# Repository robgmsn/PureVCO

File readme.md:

View this project on [CADLAB.io](https://cadlab.io/project/24199). 

DESIGN STATUS: Awaiting testing - Ready for beta testing.

VCO Updated to V3.1 14/04/21.

Mixer section changed from Average to Sum. Mix Out is now inversion of individual outs. Might be useful?
Resistor values around mixer section reduced to 10k, inline with low noise techniques.

To do:
Final test build

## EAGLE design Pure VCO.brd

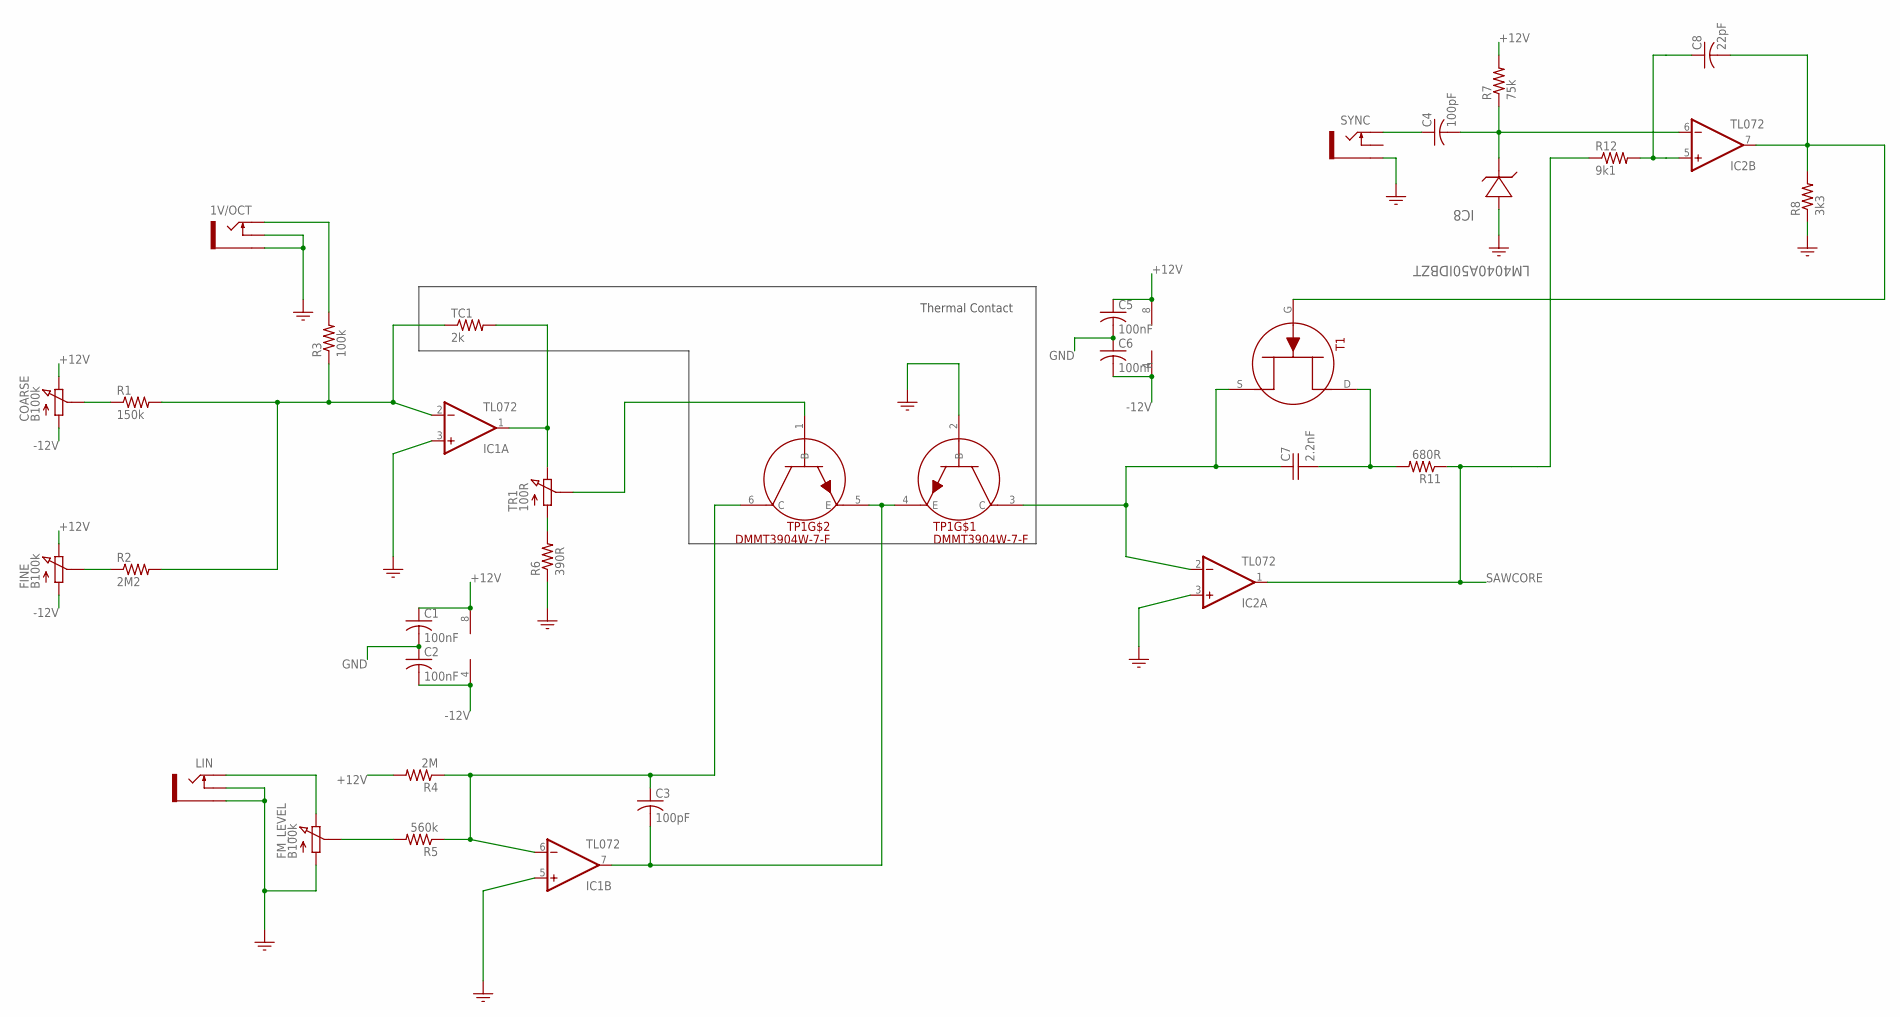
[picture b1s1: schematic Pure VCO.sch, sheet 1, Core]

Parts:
1V/OCT: PJ301M-12
C1, C2, C5, C6: 100nF; C0805
C3, C4: 100pF; C0805
C7: 2.2nF; POLY_CAP
C8: 22pF; C0805
COARSE: B100k; POT_9MM_RED_KNOB
FINE: B100k; POT_9MM_RED_MXR_KNOB
FM_LEVEL: B100k; POT_9MM_GREEN_KNOB
IC1, IC2: TL072; SO08
IC8: LM4040A50IDBZT; SOT95P237X112-3N
LIN: PJ301M-12
R1: 150k; R0805
R2: 2M2; R0805
R3: 100k; R0805
R4: 2M; R0805
R5: 560k; R0805
R6: 390R; R0805
R7: 75k; R0805
R8: 3k3; R0805
R11: 680R; R0805
R12: 9k1; R0805
SYNC: PJ301M-12
T1: MMBFJ309; N_CHN
TC1: 2k; 0207/8.5
TP1: DMMT3904W-7-F; TRANS_PAIR
TR1: 100R; TRIMMER_TH

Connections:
+12V: C1.1, C5.1, COARSE.P$3 (3), FINE.P$3 (3), IC1.8 (V+), IC2.8 (V+), R4.2, R7.2; also elsewhere on the board
-12V: C2.2, C6.2, COARSE.P$1 (1), FINE.P$1 (1), IC1.4 (V-), IC2.4 (V-); also elsewhere on the board
GND: 1V/OCT.GND (SLEEVE), 1V/OCT.NORM (SWITCH), C1.2, C2.1, C5.2, C6.1, FM_LEVEL.P$1 (1), IC1.3 (+IN), IC1.5 (+IN), IC2.3 (+IN), IC8.2 (ANODE), LIN.GND (SLEEVE), LIN.NORM (SWITCH), R6.1, R8.1, SYNC.GND (SLEEVE), TP1.2 (B); also elsewhere on the board
unnamed: COARSE.P$2 (2), R1.1
unnamed: IC1.2 (-IN), R1.2, R2.2, R3.1, TC1.1
unnamed: FINE.P$2 (2), R2.1
unnamed: IC1.1 (OUT), TC1.2, TR1.3
unnamed: R6.2, TR1.1
unnamed: 1V/OCT.TIP, R3.2
unnamed: TP1.1 (B), TR1.2
unnamed: C7.2 (-), R11.2, T1.D
unnamed: C3.1, IC1.6 (-IN), R4.1, R5.1, TP1.6 (C)
unnamed: C7.1 (+), IC2.2 (-IN), T1.S, TP1.3 (C)
unnamed: FM_LEVEL.P$3 (3), LIN.TIP
unnamed: C8.1, IC2.5 (+IN), R12.2
unnamed: FM_LEVEL.P$2 (2), R5.2
unnamed: C3.2, IC1.7 (OUT), TP1.4 (E), TP1.5 (E)
unnamed: C8.2, IC2.7 (OUT), R8.2, T1.G
unnamed: C4.1, SYNC.TIP
unnamed: C4.2, IC2.6 (-IN), IC8.1 (CATHODE), R7.1
SAWCORE: IC2.1 (OUT), R11.1, R12.1; also elsewhere on the board

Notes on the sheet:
Thermal Contact

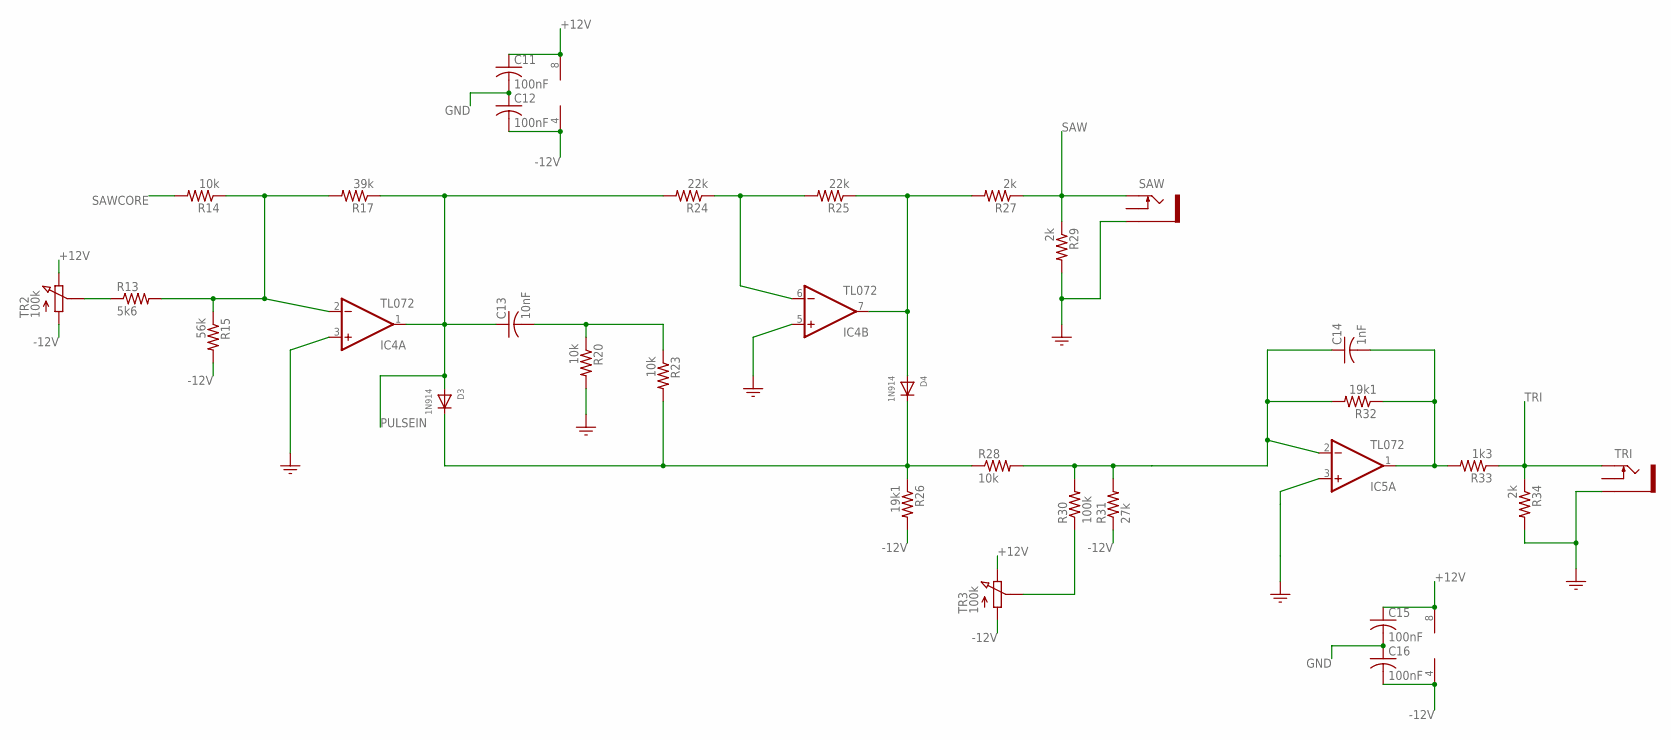
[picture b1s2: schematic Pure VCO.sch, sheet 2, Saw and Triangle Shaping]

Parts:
C11, C12, C15, C16: 100nF; C0805
C13: 10nF; C0805
C14: 1nF; C0805
D3, D4: 1N914; SOD-323F
IC4, IC5: TL072; SO08
R13: 5k6; R0805
R14, R20, R23, R28: 10k; R0805
R15: 56k; R0805
R17: 39k; R0805
R24, R25: 22k; R0805
R26, R32: 19k1; R0805
R27, R29, R34: 2k; R0805
R30: 100k; R0805
R31: 27k; R0805
R33: 1k3; R0805
SAW: PJ301M-12
TR2, TR3: 100k; TRIMMER_TH
TRI: PJ301M-12

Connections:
+12V: C11.1, C15.1, IC4.8 (V+), IC5.8 (V+), TR2.3, TR3.3; also elsewhere on the board
-12V: C12.2, C16.2, IC4.4 (V-), IC5.4 (V-), R15.2, R26.2, R31.1, TR2.1, TR3.1; also elsewhere on the board
GND: C11.2, C12.1, C15.2, C16.1, IC4.3 (+IN), IC4.5 (+IN), IC5.3 (+IN), R20.2, R29.2, R34.2, SAW.GND (SLEEVE), TRI.GND (SLEEVE); also elsewhere on the board
unnamed: R13.1, TR2.2
unnamed: IC4.2 (-IN), R13.2, R14.1, R15.1, R17.2
unnamed: C13.2, R20.1, R23.1
unnamed: R30.1, TR3.2
unnamed: IC4.6 (-IN), R24.1, R25.2
unnamed: D4.A, IC4.7 (OUT), R25.1, R27.2
unnamed: D3.C, D4.C, R23.2, R26.1, R28.1
unnamed: C14.1, IC5.2 (-IN), R28.2, R30.2, R31.2, R32.2
unnamed: C14.2, IC5.1 (OUT), R32.1, R33.2
PULSEIN: C13.1, D3.A, IC4.1 (OUT), R17.1, R24.2; also elsewhere on the board
SAW: R27.1, R29.1, SAW.TIP; also elsewhere on the board
SAWCORE: R14.2; also elsewhere on the board
TRI: R33.1, R34.1, TRI.TIP; also elsewhere on the board

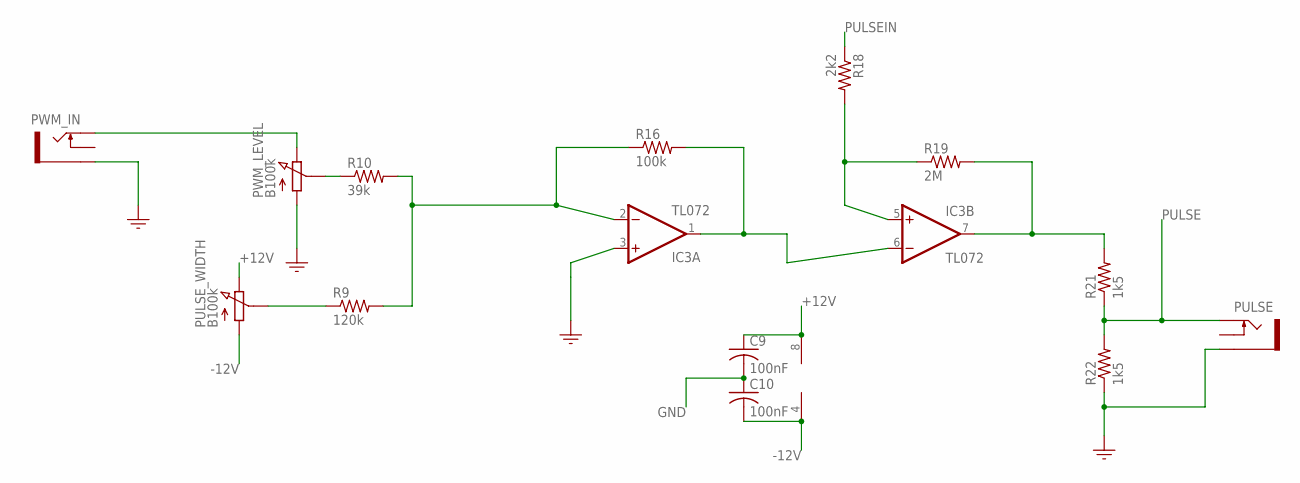
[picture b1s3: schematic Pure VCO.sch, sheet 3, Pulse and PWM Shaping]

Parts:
C9, C10: 100nF; C0805
IC3: TL072; SO08
PULSE: PJ301M-12
PULSE_WIDTH: B100k; POT_9MM_YELLOW_KNOB
PWM_IN: PJ301M-12
PWM_LEVEL: B100k; POT_9MM_GREEN_KNOB
R9: 120k; R0805
R10: 39k; R0805
R16: 100k; R0805
R18: 2k2; R0805
R19: 2M; R0805
R21, R22: 1k5; R0805

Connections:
+12V: C9.1, IC3.8 (V+), PULSE_WIDTH.P$3 (3); also elsewhere on the board
-12V: C10.2, IC3.4 (V-), PULSE_WIDTH.P$1 (1); also elsewhere on the board
GND: C9.2, C10.1, IC3.3 (+IN), PULSE.GND (SLEEVE), PWM_IN.GND (SLEEVE), PWM_LEVEL.P$1 (1), R22.1; also elsewhere on the board
unnamed: IC3.1 (OUT), IC3.6 (-IN), R16.2
unnamed: IC3.5 (+IN), R18.2, R19.1
unnamed: IC3.7 (OUT), R19.2, R21.2
unnamed: PULSE_WIDTH.P$2 (2), R9.1
unnamed: PWM_IN.TIP, PWM_LEVEL.P$3 (3)
unnamed: IC3.2 (-IN), R9.2, R10.2, R16.1
unnamed: PWM_LEVEL.P$2 (2), R10.1
PULSE: PULSE.TIP, R21.1, R22.2; also elsewhere on the board
PULSEIN: R18.1; also elsewhere on the board

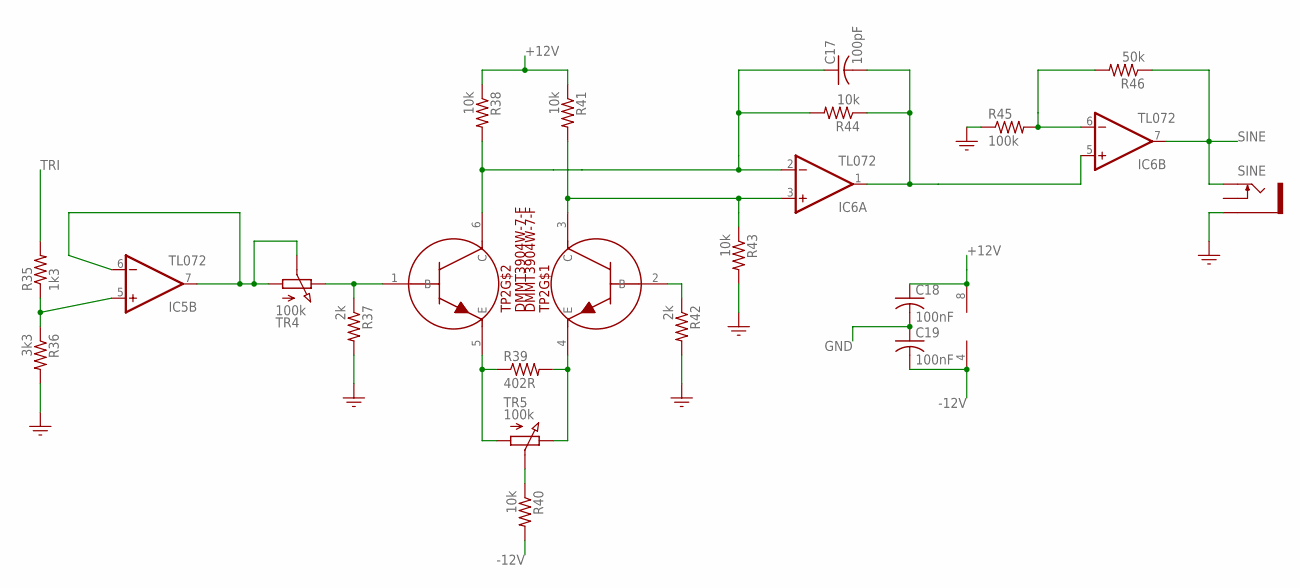
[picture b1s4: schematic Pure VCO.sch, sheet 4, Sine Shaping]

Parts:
C17: 100pF; C0805
C18, C19: 100nF; C0805
IC5, IC6: TL072; SO08
R35: 1k3; R0805
R36: 3k3; R0805
R37, R42: 2k; R0805
R38, R40, R41, R43, R44: 10k; R0805
R39: 402R; R0805
R45: 100k; R0805
R46: 50k; R0805
SINE: PJ301M-12
TP2: DMMT3904W-7-F; TRANS_PAIR
TR4, TR5: 100k; TRIMMER_TH

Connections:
+12V: C18.1, IC6.8 (V+), R38.1, R41.1; also elsewhere on the board
-12V: C19.2, IC6.4 (V-), R40.2; also elsewhere on the board
GND: C18.2, C19.1, R36.2, R37.2, R42.2, R43.2, R45.1, SINE.GND (SLEEVE); also elsewhere on the board
unnamed: C17.1, IC6.2 (-IN), R38.2, R44.2, TP2.6 (C)
unnamed: IC5.6 (-IN), IC5.7 (OUT), TR4.1, TR4.2
unnamed: R37.1, TP2.1 (B), TR4.3
unnamed: R39.1, TP2.5 (E), TR5.1
unnamed: R39.2, TP2.4 (E), TR5.3
unnamed: R40.1, TR5.2
unnamed: R42.1, TP2.2 (B)
unnamed: IC6.3 (+IN), R41.2, R43.1, TP2.3 (C)
unnamed: IC5.5 (+IN), R35.1, R36.1
unnamed: IC6.6 (-IN), R45.2, R46.2
SINE: IC6.7 (OUT), R46.1, SINE.TIP; also elsewhere on the board
SINE_PRE1: C17.2, IC6.1 (OUT), IC6.5 (+IN), R44.1
TRI: R35.2; also elsewhere on the board

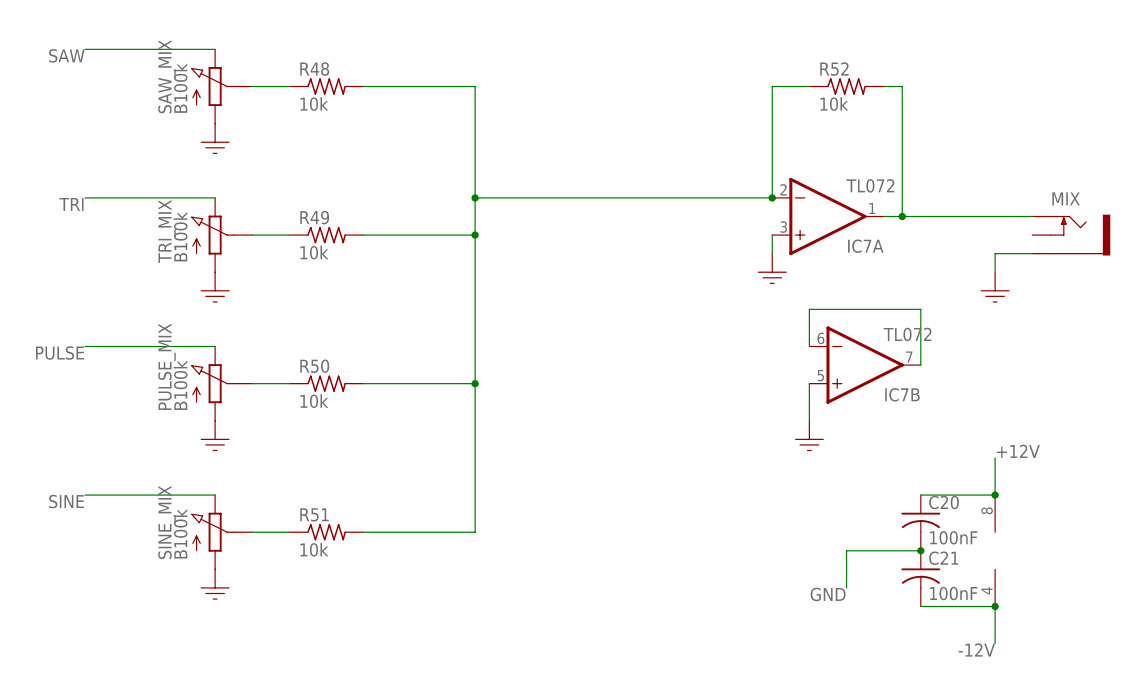
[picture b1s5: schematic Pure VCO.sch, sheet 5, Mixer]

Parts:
C20, C21: 100nF; C0805
IC7: TL072; SO08
MIX: PJ301M-12
PULSE_MIX: B100k; POT_9MM_BLUE_KNOB
R48, R49, R50, R51, R52: 10k; R0805
SAW_MIX: B100k; POT_9MM_BLUE_KNOB
SINE_MIX: B100k; POT_9MM_BLUE_KNOB
TRI_MIX: B100k; POT_9MM_BLUE_KNOB

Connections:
+12V: C20.1, IC7.8 (V+); also elsewhere on the board
-12V: C21.2, IC7.4 (V-); also elsewhere on the board
GND: C20.2, C21.1, IC7.3 (+IN), IC7.5 (+IN), MIX.GND (SLEEVE), PULSE_MIX.P$1 (1), SAW_MIX.P$1 (1), SINE_MIX.P$1 (1), TRI_MIX.P$1 (1); also elsewhere on the board
unnamed: IC7.6 (-IN), IC7.7 (OUT)
unnamed: R48.1, SAW_MIX.P$2 (2)
unnamed: R49.1, TRI_MIX.P$2 (2)
unnamed: PULSE_MIX.P$2 (2), R50.1
unnamed: R51.1, SINE_MIX.P$2 (2)
unnamed: IC7.2 (-IN), R48.2, R49.2, R50.2, R51.2, R52.1
unnamed: IC7.1 (OUT), MIX.TIP, R52.2
PULSE: PULSE_MIX.P$3 (3); also elsewhere on the board
SAW: SAW_MIX.P$3 (3); also elsewhere on the board
SINE: SINE_MIX.P$3 (3); also elsewhere on the board
TRI: TRI_MIX.P$3 (3); also elsewhere on the board

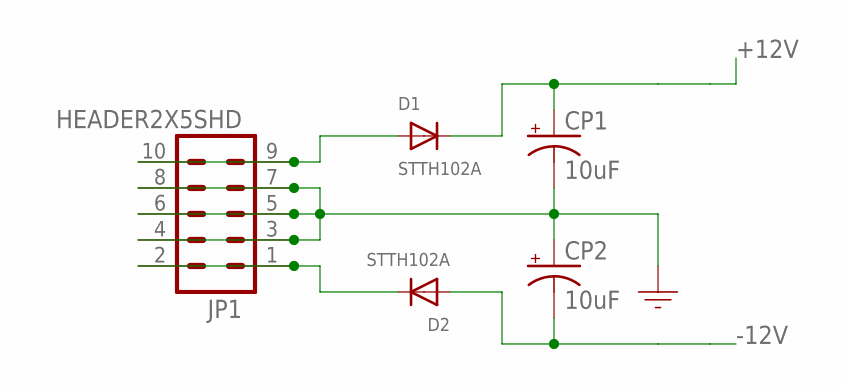
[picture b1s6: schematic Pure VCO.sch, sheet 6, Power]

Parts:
CP1, CP2: 10uF; 153CLV-0505
D1, D2: STTH102A; SMADIODE
JP1: HEADER2X5SHD; 2X5-SHROUDED

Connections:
+12V: CP1.+, D1.C; also elsewhere on the board
-12V: CP2.-, D2.A; also elsewhere on the board
GND: CP1.-, CP2.+, JP1.3, JP1.4, JP1.5, JP1.6, JP1.7, JP1.8; also elsewhere on the board
unnamed: D1.A, JP1.9, JP1.10
unnamed: D2.C, JP1.1, JP1.2

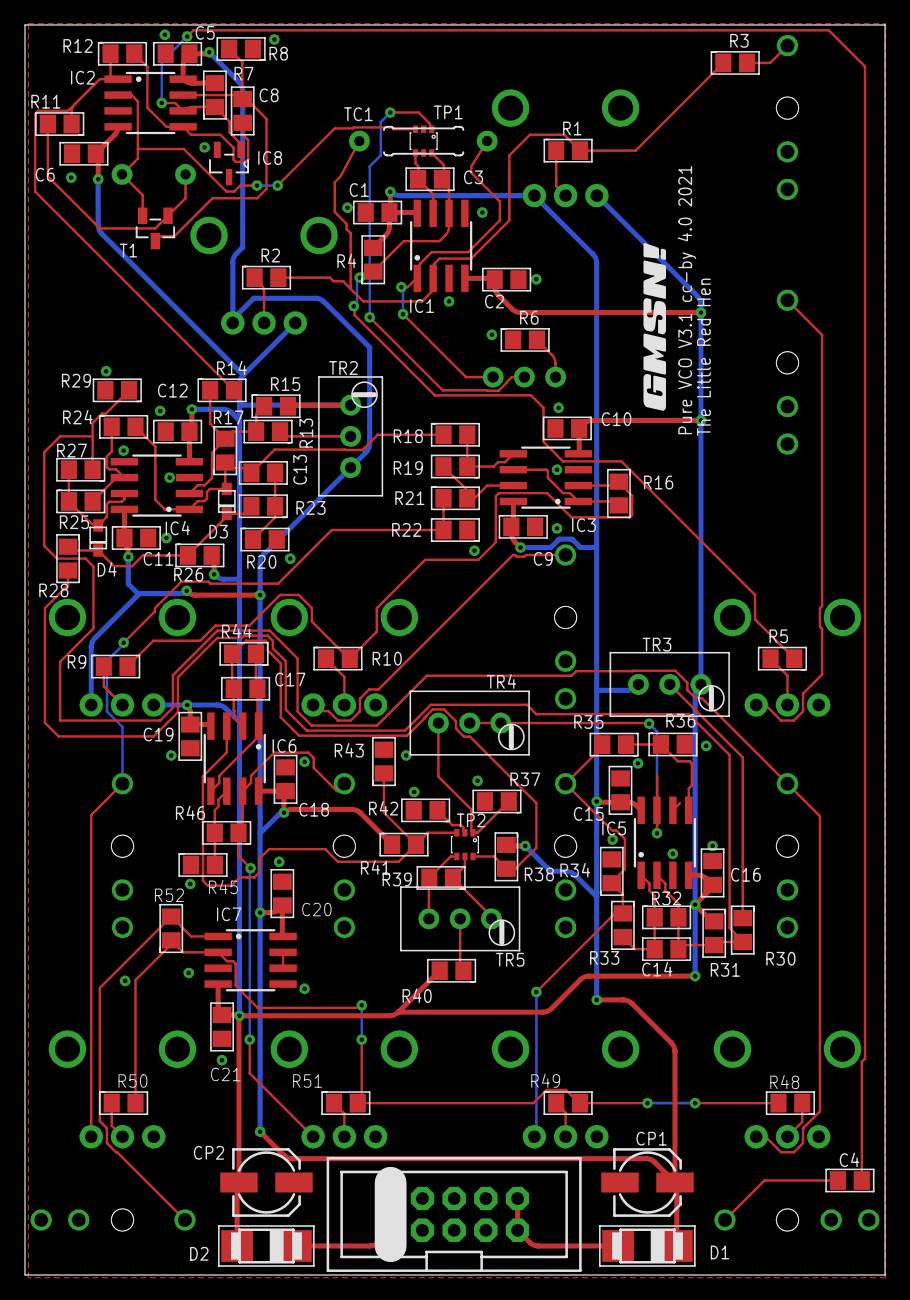
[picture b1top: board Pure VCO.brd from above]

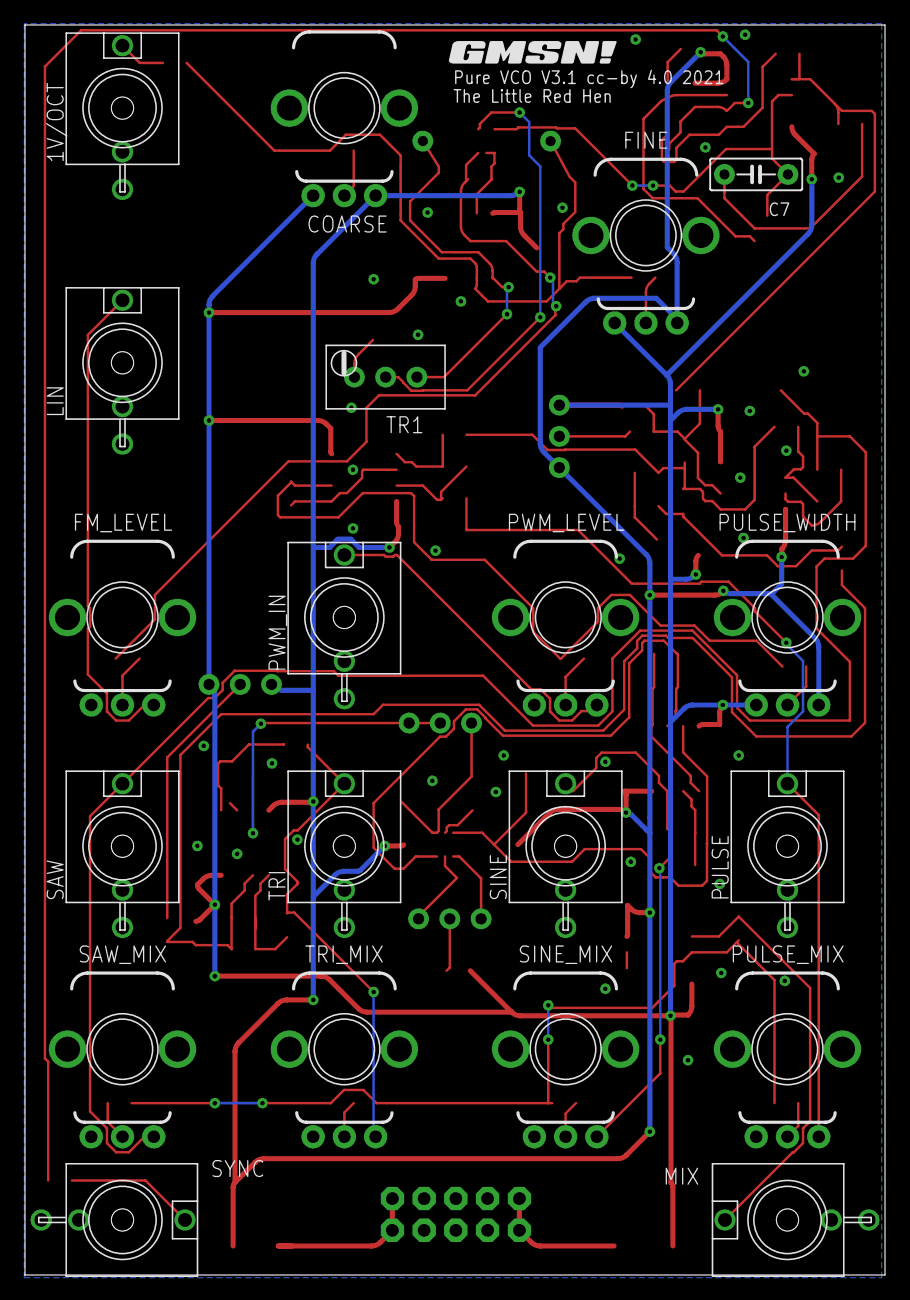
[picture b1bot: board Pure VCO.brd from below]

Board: 2 copper layers, 68.8 x 100.0 mm, 116 parts (21 on the bottom side), 62 nets.

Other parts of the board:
U$1, U$2: GMSN!_LOGO

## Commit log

2021-04-16 VCO 2.0
2021-04-16 VCO 2.1
2021-04-16 VCO 2.3
2021-04-16 VCO 3.0
2021-04-16 VCO 3.1
    VCO Updated to V3.1 14/04/21.
    Mixer section changed from Average to Sum. Mix Out is now inversion of individual outs. Might be useful?
    Resistor values around mixer section reduced to 10k, inline with low noise techniques.
2021-04-16 Backlink to CADLAB.io has been added.
2021-07-07 Reinstall

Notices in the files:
Pure VCO.brd:
Pure VCO V3.1 cc-by 4.0 2021
